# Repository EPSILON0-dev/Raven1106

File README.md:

# Raven1106

Raspberry Pi-like single board computer based on the Rockchip RV1106G3.

|  |  |
| - | - |
| | |

## Overview

Raven1106 is a custom open-hardware SBC. This repository contains everything
related to the project including: the board schematics and the PCB design, build
scripts, configurations, device trees and file system overlays for the
operating system images and all the patches needed to get everything working.

- CPU: Single-core Cortex-A7 @ 1.6 GHz
- RAM: 256MB DDR3L @ 924MHz
- Storage: SD card
- Ethernet: Full-size 100 MBit/s Ethernet port
- USB: Four USB-A ports routed through CH334F or one OTG USB-C port
- WiFi: ESP32C6 with ESP-Hosted firmware (_currently not functional_)
- Kernel: Linux 5.10 (Rockchip BSP)
- U-Boot: 2017.09 (Rockchip BSP)
- OS images: Debian 12 (bookworm, armhf)

## Why does it exist?

TLDR: It's a learning project

> The main goal of this project was to be a learning experience for designing complex high-speed digital PCBs. Creating an SBC that is almost capable enough to do basic tasks like hosting simple servers or running AI harnesses is a nice bonus. RV1106 was chosen specifically for its simplicity, integrated RAM meant no DDR routing and QFN package meant I could solder the board manually relatively easily.

> What this chip lacked in the hardware it made up for in the software side of things -- BSP is absolutely terrible, outdated, barely documented (_though with a lot of spelling mistakes_). Programming it wasn't much better either with only a few barely working flashing tools and a USB controller that might not actually be compliant with the USB spec, as most machines can't even enumerate it. It might have been genuinely easier to make this project around a more complex BGA part than this SoC.

## PCB

The board is designed in KiCad (4-layer). `pcb/` contains two revisions:

- `pcb/v1.0` — first revision
- `pcb/v1.1` — revision with component value fixes (no PCB layout changes)

| Layer 1 - Signal | Layer 2 - Ground Plane | Layer 3 - Power Planes | Layer 4 - Signal |
| :-: | :-: | :-: | :-: |
|  |  |  |  |

### Known v1.0 hardware issues and their fixes

**USB Impedance Miscalculation** - Turns out that FSUSB42MUX doesn't act as a retransmitter but like a normal switch which adds ~10 ohm impedance to the line. **Fix:** Swap `RN301` with 0-ohm and change `R301` and `R302` from 22 ohm to 10 ohm. This results the line impedance that is well in spec.

**No pullups on FSPI Flash** - Speaks for itself, thankfully the RV1106 has internal pull-ups that enable the chip and disable the write protection. And we don't even use it so it's a non-issue. _Cannot fix this without board changes._

**LED resistors too small** - The LEDs shine too brightly with 1k resistors. **Fix:** Change `R3`, `R4` and `R5` from 1k to 10k resistors.

**USB Hub crystal load too large** - The CH334F is designed to work with a crystal with no load caps, adding them causes the oscillation to die down. **Fix:** Change `R309` from 1k to 10 ohm, remove `C302` and `C303`.

**Boot button pull-up too strong** - With 1k the button does not affect the chip's boot at all. **Fix:** Change `R6` from 1k to 10k.

**Wrong ESP_BOOT pin exposed** - It should be pin 9, not pin 8. **Fix:** No way to fix it without modifying the board unfortunately, just flash the bootloader before soldering the ESP.

**Reference clock not connected to the camera** - Turns out not all camera modules have their own crystal oscillators. SC3336 requires a reference clock; RV1106 has two reference clock outputs, one of them is connected to the camera's reset and the other one to the IMU interrupt pin. **Fix:** Add a jumper from `R508` to `R515`.

> Most of these problems could have been prevented with "RTFM" (Reading The F***ing Manual).

## Repository layout

| Path | Contents |
|---|---|
| `configs/` | Defconfigs (kernel, U-Boot, crosstool-ng), device tree source, SD image layout, U-Boot env, user table |
| `kernel/` | Linux 5.10 Rockchip BSP kernel |
| `uboot/` | U-Boot 2017.09 Rockchip BSP |
| `debian/`, `overlayfs/` | Debian rootfs staging area and overlay |
| `crosstool-ng/`, `legacy-toolchain/` | Legacy uClibc toolchain (kernel/U-Boot builds) |
| `esp-hosted/` | ESP32-C6 host driver source (esp_hosted_ng) |
| `rkbin/` | Rockchip binary blobs (DDR init, trust) |
| `scripts/build.sh` | Image assembly, Debian rootfs, Docker environment |
| `images/` | Build artifacts and final `sdcard.img` |
| `pcb/` | KiCad hardware design |
| `docs/` | RV1106 datasheet / reference manuals |

## Building

### Build environment

All builds run inside a Docker container. The first invocation builds the
`rv1106-build` image, then drops you into a shell with the repository
mounted at `/work`:

```sh
make docker
```

### Toolchain

Before building any image build the legacy toolchain for the Kernel and U-Boot.
```sh
make toolchain
```

### Debian image

```sh
make            # default target: debian-image
# or explicitly:
make debian-image
```

> Known issue: If build fails on stage 2 debootstrap because of "Invalid format", just delete the `debian/` directory, restart the container and try to build again. _It does that sometimes..._

This builds the kernel, device tree, and U-Boot, then creates a Debian 12
(bookworm, armhf) rootfs with debootstrap (using qemu-user-static/binfmt for
the second stage) and assembles `images/sdcard.img`.

Notes:

- Default login: user `debian`, password `raven` (sudo user, SSH enabled).
  Override with the `BOARD_USER` and `DEBIAN_PASSWORD` environment variables.
- Included packages: systemd, ifupdown, openssh-server, sudo, dhcp client,
  busybox, vim-tiny, ca-certificates (see `DEBIAN_PACKAGES` in
  `scripts/build.sh`).
- Rootfs image size: 1 GB (`DEBIAN_ROOTFS_SIZE`).
- For now there's no autoresize, run `sudo resize2fs /dev/mmcblk1p5` after
  the first boot.

### Component targets

| Target | Description |
|---|---|
| `make kernel` | Build the kernel using the legacy toolchain |
| `make dtb` | Preprocess and compile `configs/device-tree.dts` into `images/` |
| `make uboot` | Build U-Boot (SPL + idblock + uboot.img) |
| `make espdriver` | Build the ESP32-C6 host driver against the kernel |
| `make toolchain` | Build the crosstool-ng uClibc toolchain |
| `make docker` | Build/enter the Docker build environment |
| `make *-clean` | Clean kernel / U-Boot build trees |

### Configuration targets

Each of these copies the stored defconfig from `configs/`, opens
`menuconfig`, and saves the result back to `configs/`:

```sh
make kernel-config
make uboot-config
make toolchain-config
```

## Output artifacts

All artifacts land in `images/`:

| File | Description |
|---|---|
| `sdcard.img` | Final flashable SD card image |
| `download.bin`, `idblock.img`, `uboot.img` | Bootloader stages |
| `Image`, `zImage`, `device-tree.dtb` | Kernel and device tree |
| `env.img` | U-Boot environment (from `configs/image-env.txt`) |
| `boot.vfat` | FAT32 boot partition (kernel + dtb) |
| `rootfs.ext4`, `rootfs.tar` | Root filesystem |

### SD card layout

The image has no MBR/GPT; partitions are defined by the kernel command line
(`blkdevparts`, see `configs/sdcard-image.cfg` and `configs/image-env.txt`):

| Partition | Offset | Size | Contents |
|---|---|---|---|
| env | 0x0 | 32 KiB | U-Boot environment |
| idblock | 0x8000 | 512 KiB | Rockchip ID block (SPL) |
| uboot | 0x88000 | 256 KiB | U-Boot |
| boot | 4 MiB | 64 MiB | FAT32: kernel image + device tree |
| rootfs | 68 MiB | remainder | ext4 root filesystem |

## Flashing and first boot

```sh
sudo dd if=images/sdcard.img of=/dev/sdX bs=4M status=progress conv=fsync
```

Serial console: `ttyFIQ0` at 115200 baud.

## WiFi setup

The WiFi interface (ESP32-C6 running ESP-Hosted firmware over SDIO) is set up
at boot on a running system, it is not configured during the image build. The
helper script `overlayfs/usr/local/bin/start-network` (installed on the image
at `/usr/local/bin/start-network`) performs the entire sequence:

1. **Module reset** - GPIO 2 is exported, pulsed low and released, which
   resets the ESP32. The pin is then unexported and the script waits 2 s.
2. **Driver loading** - the required modules are inserted from
   `/lib/modules/5.10.252/`: the crypto primitives (`libaes`, `libarc4`,
   `ecc`, `ecdh_generic`), `bluetooth`, the wireless stack (`cfg80211`) and
   finally the ESP-Hosted SDIO host driver (`esp32_sdio.ko`). The script then
   waits 5 s for the module to appear as `wlan0`.
   (The host driver is built separately with `make espdriver`.)
3. **Association** - `wpa_passphrase <ssid> <password>` generates a config
   into `/tmp/wpa.conf` and `wpa_supplicant -iwlan0` is started in the
   background, followed by a 15 s wait for the connection to come up.
4. **Addressing** - static IP configuration:
   `192.168.0.100/24` on `wlan0` with the default route via `192.168.0.1`.

### Configuring the network

The SSID, passphrase and addresses are hardcoded in
`/usr/local/bin/start-network`, so edit them on the board (or in
`overlayfs/usr/local/bin/start-network` and rebuild/flash the image):

```sh
sudo vi /usr/local/bin/start-network
```

Replace `ssid` and `password` in the `wpa_passphrase` call with your network
name and passphrase, and adjust the `ip addr add` and `ip route replace
default via` lines for your address and gateway. There is no DHCP client call
for `wlan0`.

### systemd service

The script runs automatically at boot via the systemd unit
`overlayfs/etc/systemd/system/start-network.service`
(`/etc/systemd/system/start-network.service` on the image) - a `oneshot`
service started after `network.target`, running as root with
`RemainAfterExit=yes`, and logging all output to `/tmp/wifi.log`. Use it to
start/stop the WiFi bring-up manually or to check the log:

```sh
sudo systemctl start start-network
sudo systemctl status start-network
less /tmp/wifi.log
```

> Note: the ESP32 must already carry the ESP-Hosted firmware (flash the
> bootloader/ESP before soldering it, see the PCB section above).

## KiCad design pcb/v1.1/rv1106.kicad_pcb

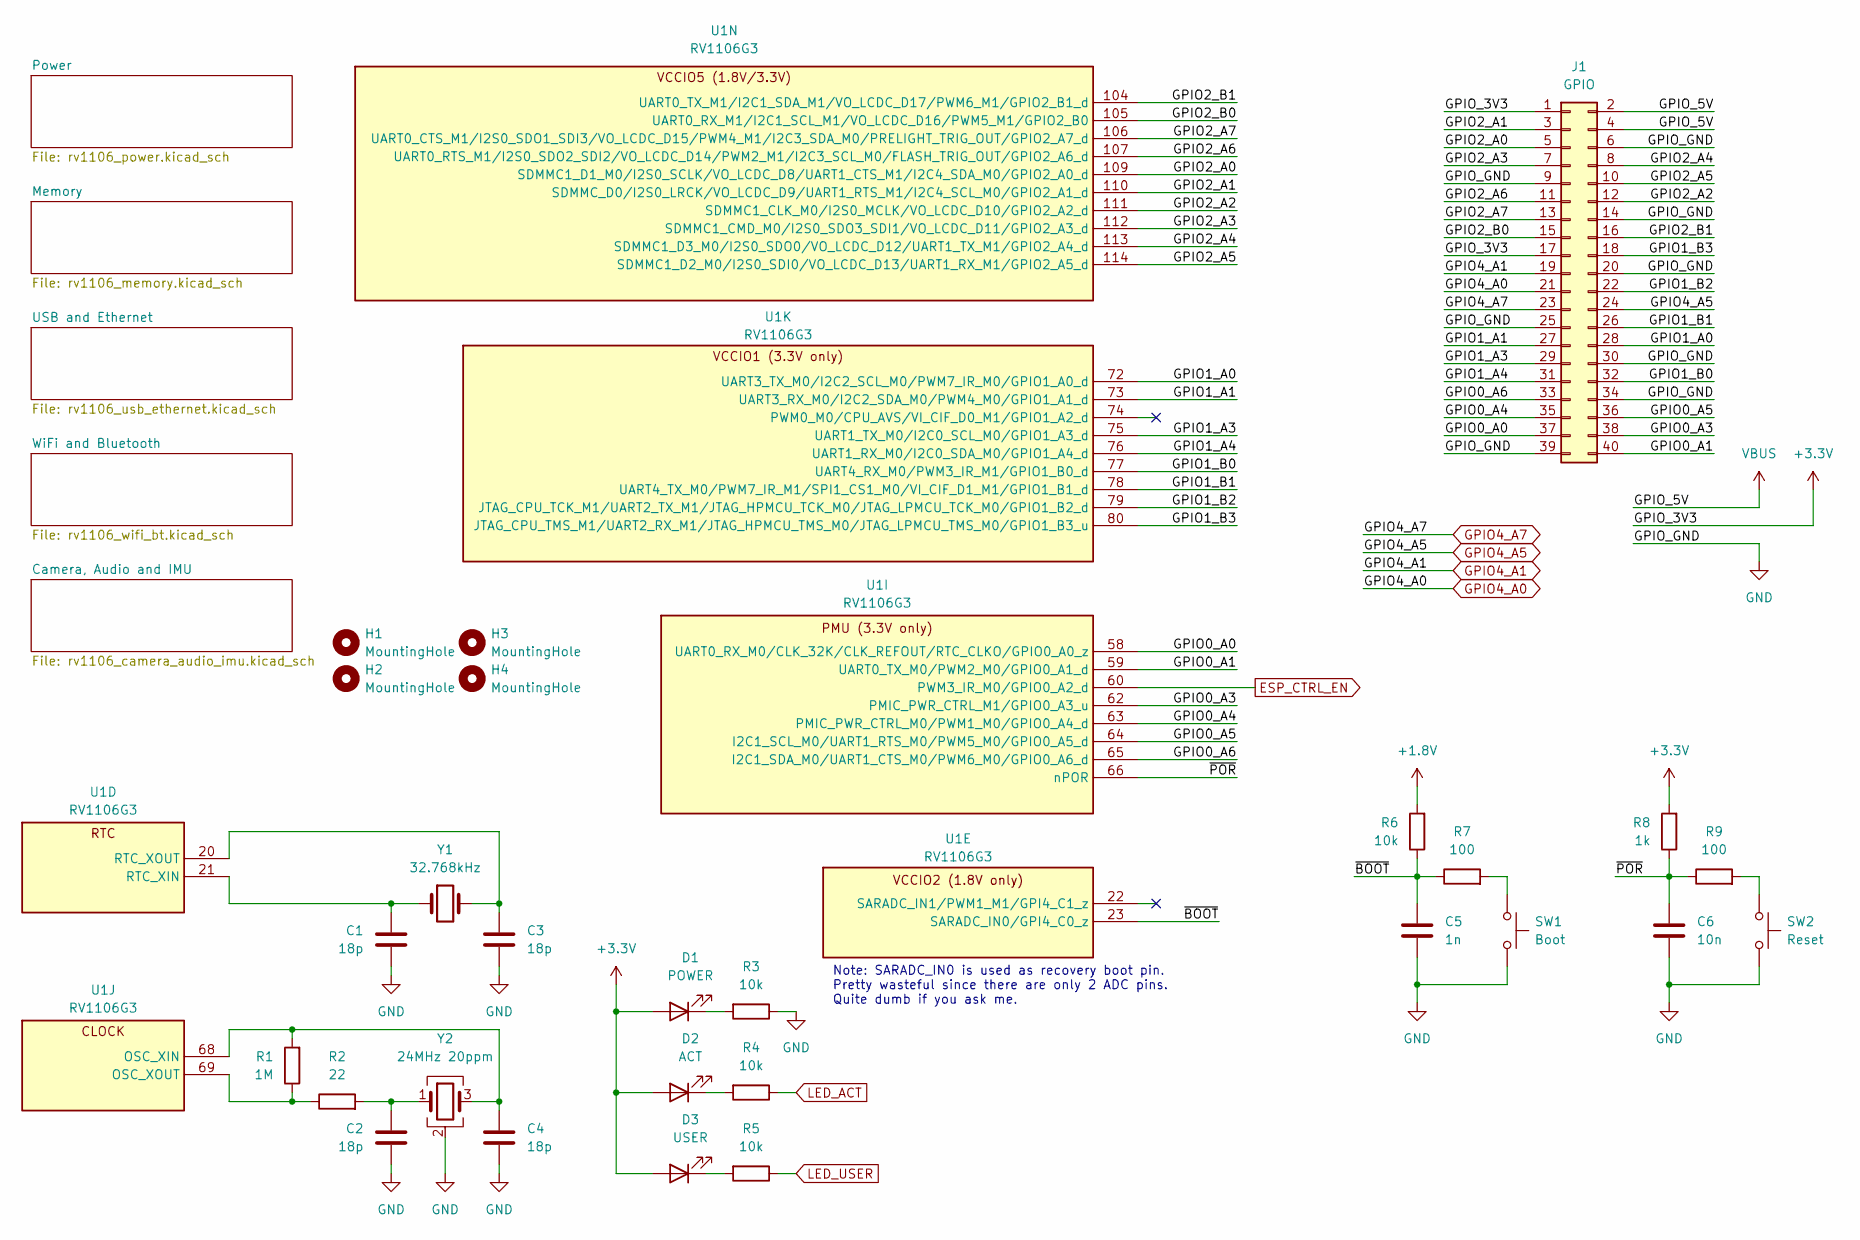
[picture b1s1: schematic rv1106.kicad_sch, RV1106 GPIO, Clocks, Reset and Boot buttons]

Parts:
C1, C2, C3, C4: 18p; C_0402_1005Metric; LCSC C7393840
C5: 1n; C_0402_1005Metric; LCSC C6119789
C6: 10n; C_0402_1005Metric; LCSC C696856
D1: POWER; LED_0603_1608Metric
D2: ACT; LED_0603_1608Metric
D3: USER; LED_0603_1608Metric
H1, H2, H3, H4: MountingHole; MountingHole_2.7mm_M2.5
J1: GPIO; PinHeader_2x20_P2.54mm_Vertical
R1: 1M; R_0402_1005Metric; LCSC C3017524
R2: 22; R_0402_1005Metric; LCSC C2929994
R3, R4, R5, R6: 10k; R_0402_1005Metric; LCSC C54531013
R7, R9: 100; R_0402_1005Metric; LCSC C54920716
R8: 1k; R_0402_1005Metric; LCSC C54531013
SW1: Boot; SW_Push_SPST_NO_Alps_SKRK
SW2: Reset; SW_Push_SPST_NO_Alps_SKRK
U1: RV1106G3; Rockchip_QFN-128-1EP_12.3x12.3mm_P0.35mm_EP7x7mm
Y1: 32.768kHz; Crystal_SMD_2012-2Pin_2.0x1.2mm; LCSC C2961989
Y2: 24MHz 20ppm; Crystal_SMD_2520-4Pin_2.5x2.0mm; LCSC C5261113

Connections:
+1.8V: R6.2; also elsewhere on the board
+3.3V: D1.2 (A), D2.2 (A), D3.2 (A), J1.1, J1.17, R8.2; also elsewhere on the board
/GPIO0_A0: J1.37, U1.58 (UART0_RX_M0/CLK_32K/CLK_REFOUT/RTC_CLKO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)
/GPIO0_A1: J1.40, U1.59 (UART0_TX_M0/PWM2_M0/GPIO0_A1_d)
/GPIO0_A3: J1.38, U1.62 (PMIC_PWR_CTRL_M1/GPIO0_A3_u)
/GPIO0_A4: J1.35, U1.63 (PMIC_PWR_CTRL_M0/PWM1_M0/GPIO0_A4_d)
/GPIO0_A5: J1.36, U1.64 (I2C1_SCL_M0/UART1_RTS_M0/PWM5_M0/GPIO0_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)
/GPIO0_A6: J1.33, U1.65 (I2C1_SDA_M0/UART1_CTS_M0/PWM6_M0/GPIO0_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)
/GPIO1_A0: J1.28, U1.72 (UART3_TX_M0/I2C2_SCL_M0/PWM7_IR_M0/GPIO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)
/GPIO1_A1: J1.27, U1.73 (UART3_RX_M0/I2C2_SDA_M0/PWM4_M0/GPIO1_A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)
/GPIO1_A3: J1.29, U1.75 (UART1_TX_M0/I2C0_SCL_M0/GPIO1_A3_d)
/GPIO1_A4: J1.31, U1.76 (UART1_RX_M0/I2C0_SDA_M0/GPIO1_A4_d)
/GPIO1_B0: J1.32, U1.77 (UART4_RX_M0/PWM3_IR_M1/GPIO1_B0_d)
/GPIO1_B1: J1.26, U1.78 (UART4_TX_M0/PWM7_IR_M1/SPI1_CS1_M0/VI_C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)
/GPIO1_B2: J1.22, U1.79 (JTAG_CPU_TCK_M1/UART2_TX_M1/JTAG_HPMCU_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)
/GPIO1_B3: J1.18, U1.80 (JTAG_CPU_TMS_M1/UART2_RX_M1/JTAG_HPMCU_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)
/GPIO2_A0: J1.5, U1.109 (SDMMC1_D1_M0/I2S0_SCLK/VO_LCDC_D8/UART1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)
/GPIO2_A1: J1.3, U1.110 (SDMMC_D0/I2S0_LRCK/VO_LCDC_D9/UART1_RTS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)
/GPIO2_A2: J1.12, U1.111 (SDMMC1_CLK_M0/I2S0_MCLK/VO_LCDC_D10/GPI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)
/GPIO2_A3: J1.7, U1.112 (SDMMC1_CMD_M0/I2S0_SDO3_SDI1/VO_LCDC_D1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)
/GPIO2_A4: J1.8, U1.113 (SDMMC1_D3_M0/I2S0_SDO0/VO_LCDC_D12/UART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)
/GPIO2_A5: J1.10, U1.114 (SDMMC1_D2_M0/I2S0_SDI0/VO_LCDC_D13/UART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)
/GPIO2_A6: J1.11, U1.107 (UART0_RTS_M1/I2S0_SDO2_SDI2/VO_LCDC_D14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)
/GPIO2_A7: J1.13, U1.106 (UART0_CTS_M1/I2S0_SDO1_SDI3/VO_LCDC_D15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)
/GPIO2_B0: J1.15, U1.105 (UART0_RX_M1/I2C1_SCL_M1/VO_LCDC_D16/PWM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)
/GPIO2_B1: J1.16, U1.104 (UART0_TX_M1/I2C1_SDA_M1/VO_LCDC_D17/PWM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)
/~BOOT: C5.1, R6.1, R7.1, U1.23 (SARADC_IN0/GPI4_C0_z)
/~POR: C6.1, R8.1, R9.1, U1.66 (nPOR)
ESP_CTRL_EN: U1.60 (PWM3_IR_M0/GPIO0_A2_d); also elsewhere on the board
GND: C1.2, C2.2, C3.2, C4.2, C5.2, C6.2, J1.6, J1.9, J1.14, J1.20, J1.25, J1.30, J1.34, J1.39, R3.1, SW1.2, SW2.2, Y2.2 (G), Y2.4 (G); also elsewhere on the board
GPIO4_A0: J1.21; also elsewhere on the board
GPIO4_A1: J1.19; also elsewhere on the board
GPIO4_A5: J1.24; also elsewhere on the board
GPIO4_A7: J1.23; also elsewhere on the board
LED_ACT: R4.1; also elsewhere on the board
LED_USER: R5.1; also elsewhere on the board
unnamed: C2.1, R2.2, Y2.1
unnamed: D1.1 (K), R3.2
unnamed: D2.1 (K), R4.2
unnamed: D3.1 (K), R5.2
unnamed: R7.2, SW1.1
unnamed: R9.2, SW2.1
unnamed: C4.1, R1.2, U1.68 (OSC_XIN), Y2.3
unnamed: R1.1, R2.1, U1.69 (OSC_XOUT)
unnamed: C1.1, U1.21 (RTC_XIN), Y1.1
unnamed: C3.1, U1.20 (RTC_XOUT), Y1.2
VBUS: J1.2, J1.4; also elsewhere on the board

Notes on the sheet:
Note: SARADC_IN0 is used as recovery boot pin. Pretty wasteful since there are only 2 ADC pins. Quite dumb if you ask me.

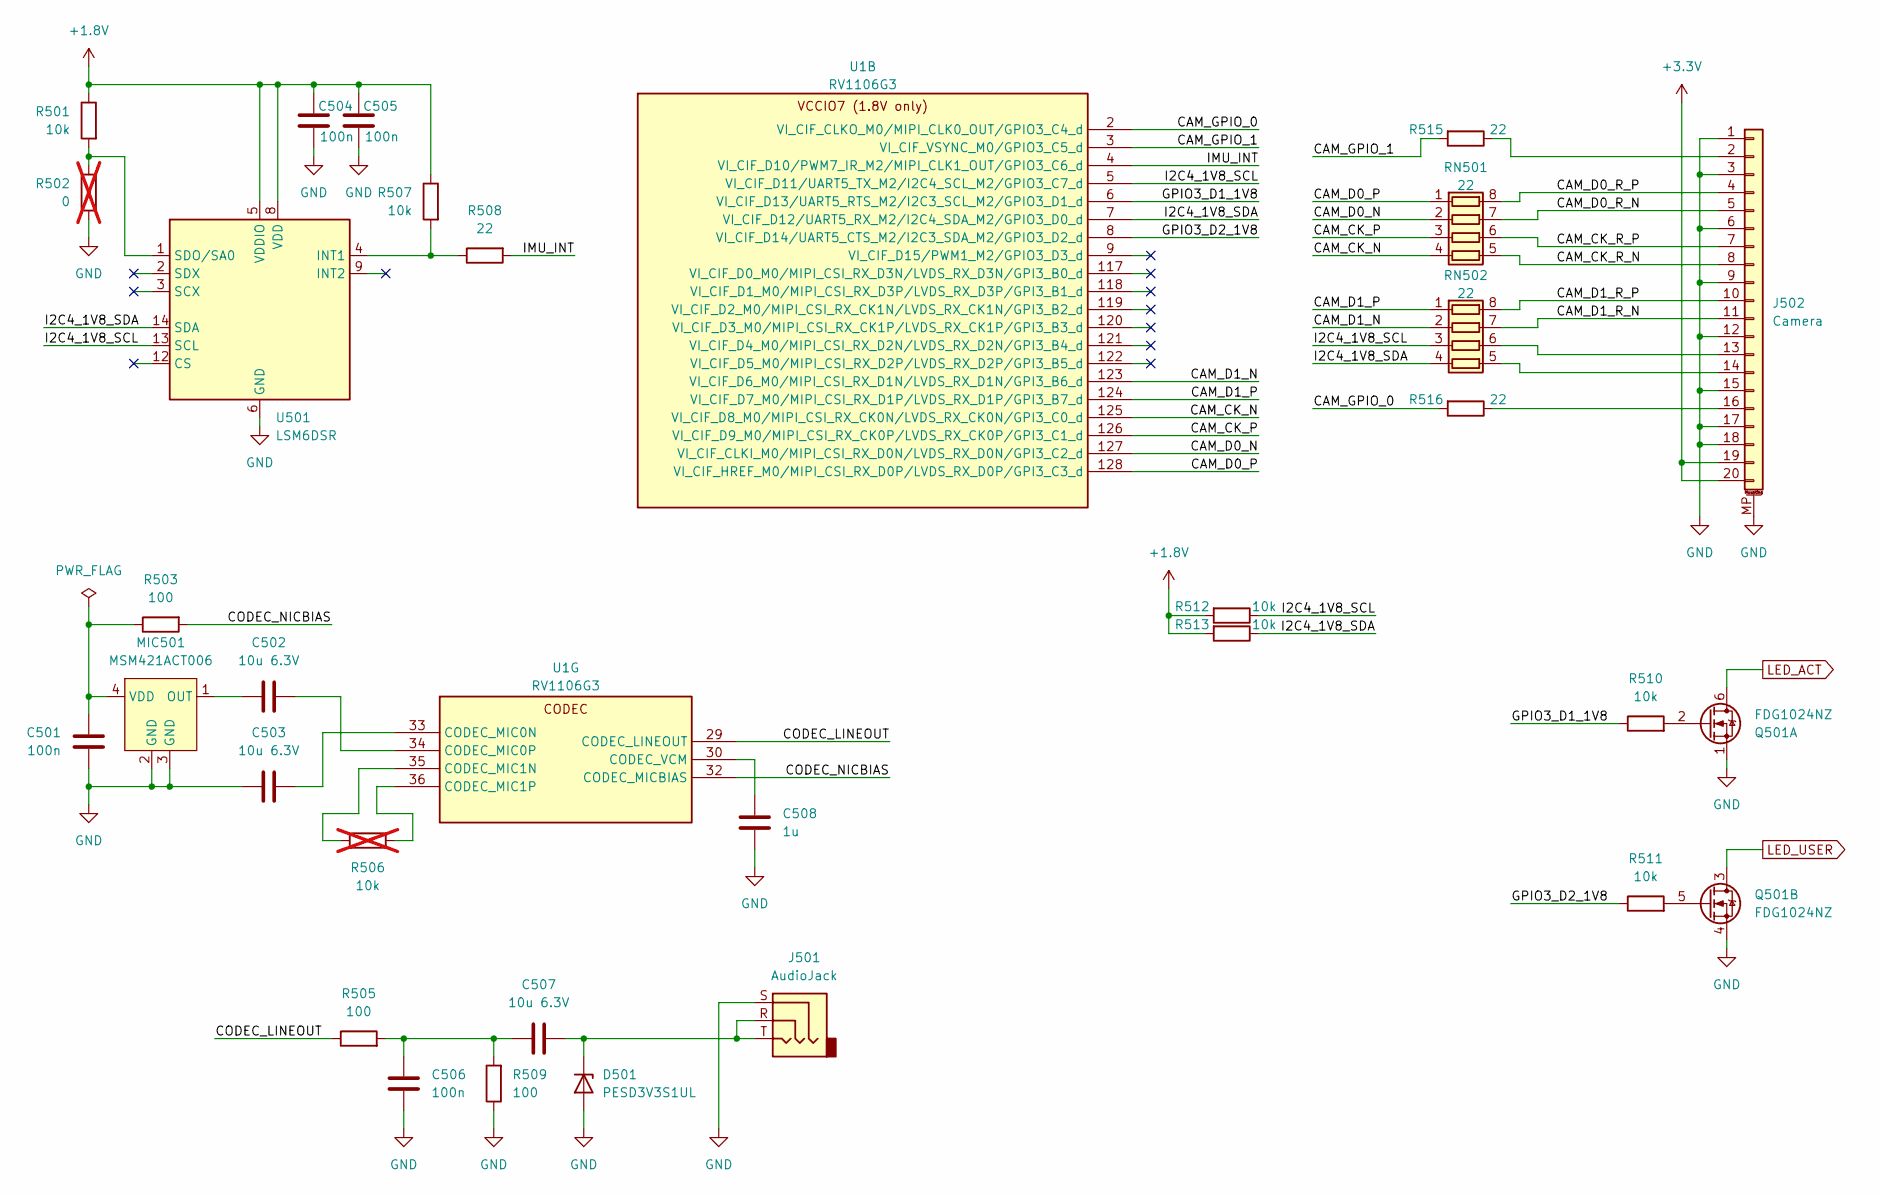
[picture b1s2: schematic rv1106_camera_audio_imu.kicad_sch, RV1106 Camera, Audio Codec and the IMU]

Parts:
C501, C504, C505, C506: 100n; C_0402_1005Metric; LCSC C3839219
C502, C503, C507: 10u 6.3V; C_0603_1608Metric; LCSC C1691
C508: 1u; C_0402_1005Metric; LCSC C380293
D501: PESD3V3S1UL; D_SOD-882; LCSC C70371
J501: AudioJack; Jack_3.5mm_CUI_SJ-3523-SMT_Horizontal; LCSC C4991872
J502: Camera; FPC_20_0.5mm_MP_BottomSide; LCSC C51364851
MIC501: MSM421ACT006; LGA4-1.9x2.8; LCSC C51928207
Q501: FDG1024NZ; SOT-363_SC-70-6; LCSC C51886163
R501, R507, R510, R511, R512, R513: 10k; R_0402_1005Metric; LCSC C54531014
R502: 0; R_0402_1005Metric; not fitted
R503, R505, R509: 100; R_0402_1005Metric; LCSC C54920716
R506: 10k; R_0402_1005Metric; not fitted
R508, R515, R516: 22; R_0402_1005Metric; LCSC C2929994
RN501, RN502: 22; R_Array_Convex_4x0402; LCSC C168184
U1: RV1106G3; Rockchip_QFN-128-1EP_12.3x12.3mm_P0.35mm_EP7x7mm
U501: LSM6DSR; LGA-14_3x2.5mm_P0.5mm_LayoutBorder3x4y

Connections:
+1.8V: C504.1, C505.1, R501.1, R507.1, R512.2, R513.2, U501.5 (VDDIO), U501.8 (VDD); also elsewhere on the board
+3.3V: J502.19, J502.20; also elsewhere on the board
/Camera, Audio and IMU/CAM_CK_N: RN501.4 (R4.1), U1.125 (VI_CIF_D8_M0/MIPI_CSI_RX_CK0N/LVDS_RX_C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)
/Camera, Audio and IMU/CAM_CK_P: RN501.3 (R3.1), U1.126 (VI_CIF_D9_M0/MIPI_CSI_RX_CK0P/LVDS_RX_C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)
/Camera, Audio and IMU/CAM_CK_R_N: J502.8, RN501.5 (R4.2)
/Camera, Audio and IMU/CAM_CK_R_P: J502.7, RN501.6 (R3.2)
/Camera, Audio and IMU/CAM_D0_N: RN501.2 (R2.1), U1.127 (VI_CIF_CLKI_M0/MIPI_CSI_RX_D0N/LVDS_RX_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)
/Camera, Audio and IMU/CAM_D0_P: RN501.1 (R1.1), U1.128 (VI_CIF_HREF_M0/MIPI_CSI_RX_D0P/LVDS_RX_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)
/Camera, Audio and IMU/CAM_D0_R_N: J502.5, RN501.7 (R2.2)
/Camera, Audio and IMU/CAM_D0_R_P: J502.4, RN501.8 (R1.2)
/Camera, Audio and IMU/CAM_D1_N: RN502.2 (R2.1), U1.123 (VI_CIF_D6_M0/MIPI_CSI_RX_D1N/LVDS_RX_D1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)
/Camera, Audio and IMU/CAM_D1_P: RN502.1 (R1.1), U1.124 (VI_CIF_D7_M0/MIPI_CSI_RX_D1P/LVDS_RX_D1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)
/Camera, Audio and IMU/CAM_D1_R_N: J502.11, RN502.7 (R2.2)
/Camera, Audio and IMU/CAM_D1_R_P: J502.10, RN502.8 (R1.2)
/Camera, Audio and IMU/CAM_GPIO_0: R516.2, U1.2 (VI_CIF_CLKO_M0/MIPI_CLK0_OUT/GPIO3_C4_d)
/Camera, Audio and IMU/CAM_GPIO_1: R515.2, U1.3 (VI_CIF_VSYNC_M0/GPIO3_C5_d)
/Camera, Audio and IMU/CODEC_LINEOUT: R505.1, U1.29 (CODEC_LINEOUT)
/Camera, Audio and IMU/CODEC_NICBIAS: R503.2, U1.32 (CODEC_MICBIAS)
/Camera, Audio and IMU/GPIO3_D1_1V8: R510.1, U1.6 (VI_CIF_D13/UART5_RTS_M2/I2C3_SCL_M2/GPI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)
/Camera, Audio and IMU/GPIO3_D2_1V8: R511.1, U1.8 (VI_CIF_D14/UART5_CTS_M2/I2C3_SDA_M2/GPI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)
/Camera, Audio and IMU/I2C4_1V8_SCL: R512.1, RN502.3 (R3.1), U1.5 (VI_CIF_D11/UART5_TX_M2/I2C4_SCL_M2/GPIO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), U501.13 (SCL)
/Camera, Audio and IMU/I2C4_1V8_SDA: R513.1, RN502.4 (R4.1), U1.7 (VI_CIF_D12/UART5_RX_M2/I2C4_SDA_M2/GPIO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), U501.14 (SDA)
/Camera, Audio and IMU/IMU_INT: R508.2, U1.4 (VI_CIF_D10/PWM7_IR_M2/MIPI_CLK1_OUT/GPI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)
GND: C501.2, C503.1, C504.2, C505.2, C506.2, C508.1, D501.2 (A), J501.S, J502.1, J502.3, J502.6, J502.9, J502.12, J502.15, J502.17, J502.18, J502.MP (MountPin), MIC501.2 (GND), MIC501.3 (GND), Q501.1 (S), Q501.4 (S), R502.2, R509.1, U501.6 (GND), U501.7 (GND); also elsewhere on the board
LED_ACT: Q501.6 (D); also elsewhere on the board
LED_USER: Q501.3 (D); also elsewhere on the board
unnamed: C506.1, C507.1, R505.2, R509.2
unnamed: C507.2, D501.1 (K), J501.R, J501.T
unnamed: J502.2, R515.1
unnamed: J502.13, RN502.6 (R3.2)
unnamed: J502.14, RN502.5 (R4.2)
unnamed: J502.16, R516.1
unnamed: C502.1, MIC501.1 (OUT)
unnamed: C501.1, MIC501.4 (VDD), R503.1
unnamed: Q501.2 (G), R510.2
unnamed: Q501.5 (G), R511.2
unnamed: C503.2, U1.33 (CODEC_MIC0N)
unnamed: C502.2, U1.34 (CODEC_MIC0P)
unnamed: R506.1, U1.35 (CODEC_MIC1N)
unnamed: R506.2, U1.36 (CODEC_MIC1P)
unnamed: C508.2, U1.30 (CODEC_VCM)
unnamed: R507.2, R508.1, U501.4 (INT1)
unnamed: R501.2, R502.1, U501.1 (SDO/SA0)

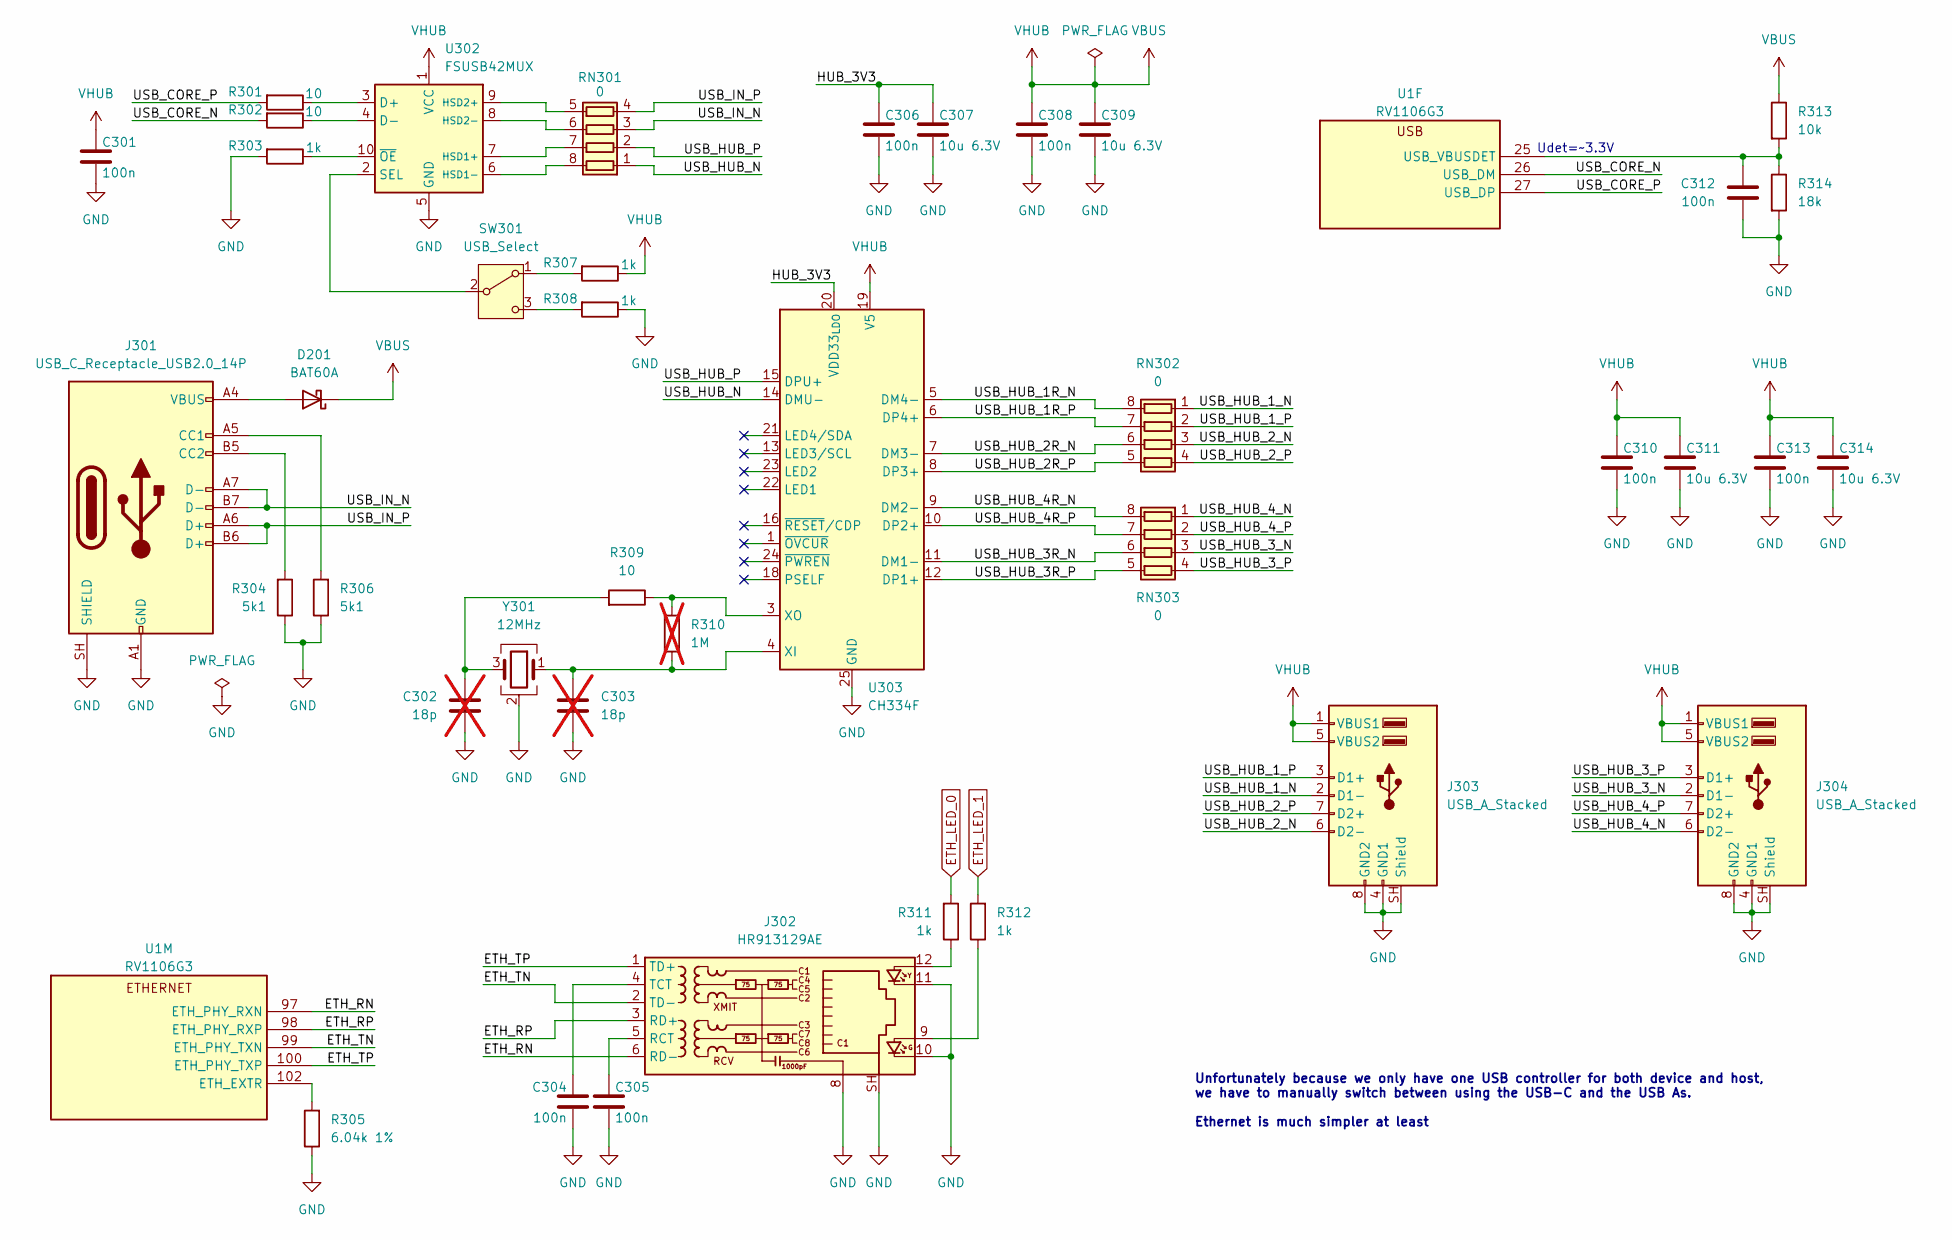
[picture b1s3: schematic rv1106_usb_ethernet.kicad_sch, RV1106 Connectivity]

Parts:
C301, C304, C305, C306, C308, C310, C312, C313: 100n; C_0402_1005Metric; LCSC C3839219
C302, C303: 18p; C_0402_1005Metric; LCSC C7393840; not fitted
C307, C309, C311, C314: 10u 6.3V; C_0603_1608Metric; LCSC C1691
D201: BAT60A; D_SOD-323; LCSC C5355496
J301: USB_C_Receptacle_USB2.0_14P; USB_C_Receptacle_G-Switch_GT-USB-7010ASV
J302: HR913129AE; RJ45_Hanrun_HR911105A_Horizontal; LCSC C95663
J303, J304: USB_A_Stacked; USB_A_Wuerth_61400826021_Horizontal_Stacked; LCSC C456021
R301, R302: 10; R_0402_1005Metric; LCSC C2929994
R303, R307, R308, R311, R312: 1k; R_0402_1005Metric; LCSC C54531013
R304, R306: 5k1; R_0402_1005Metric; LCSC C53224182
R305: 6.04k 1%; R_0402_1005Metric; LCSC C881060
R309: 10; R_0402_1005Metric; LCSC C54531013
R310: 1M; R_0402_1005Metric; not fitted
R313: 10k; R_0402_1005Metric; LCSC C54531014
R314: 18k; R_0402_1005Metric; LCSC C49653003
RN301, RN302, RN303: 0; R_Array_Convex_4x0402; LCSC C168184
SW301: USB_Select; SW_SPDT_PCM12
U1: RV1106G3; Rockchip_QFN-128-1EP_12.3x12.3mm_P0.35mm_EP7x7mm
U302: FSUSB42MUX; MSOP-10_3x3mm_P0.5mm; LCSC C11355
U303: CH334F; QFN-24-1EP_4x4mm_P0.5mm_EP2.7x2.7mm; LCSC C5187527
Y301: 12MHz; Crystal_SMD_2520-4Pin_2.5x2.0mm; LCSC C5261113

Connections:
/USB and Ethernet/ETH_RN: J302.6 (RD-), U1.97 (ETH_PHY_RXN)
/USB and Ethernet/ETH_RP: J302.3 (RD+), U1.98 (ETH_PHY_RXP)
/USB and Ethernet/ETH_TN: J302.2 (TD-), U1.99 (ETH_PHY_TXN)
/USB and Ethernet/ETH_TP: J302.1 (TD+), U1.100 (ETH_PHY_TXP)
/USB and Ethernet/HUB_3V3: C306.1, C307.1, U303.20 (VDD33_{LDO})
/USB and Ethernet/USB_CORE_N: R302.2, U1.26 (USB_DM)
/USB and Ethernet/USB_CORE_P: R301.2, U1.27 (USB_DP)
/USB and Ethernet/USB_HUB_1R_N: RN302.8 (R1.2), U303.5 (DM4-)
/USB and Ethernet/USB_HUB_1R_P: RN302.7 (R2.2), U303.6 (DP4+)
/USB and Ethernet/USB_HUB_1_N: J303.2 (D1-), RN302.1 (R1.1)
/USB and Ethernet/USB_HUB_1_P: J303.3 (D1+), RN302.2 (R2.1)
/USB and Ethernet/USB_HUB_2R_N: RN302.6 (R3.2), U303.7 (DM3-)
/USB and Ethernet/USB_HUB_2R_P: RN302.5 (R4.2), U303.8 (DP3+)
/USB and Ethernet/USB_HUB_2_N: J303.6 (D2-), RN302.3 (R3.1)
/USB and Ethernet/USB_HUB_2_P: J303.7 (D2+), RN302.4 (R4.1)
/USB and Ethernet/USB_HUB_3R_N: RN303.6 (R3.2), U303.11 (DM1-)
/USB and Ethernet/USB_HUB_3R_P: RN303.5 (R4.2), U303.12 (DP1+)
/USB and Ethernet/USB_HUB_3_N: J304.2 (D1-), RN303.3 (R3.1)
/USB and Ethernet/USB_HUB_3_P: J304.3 (D1+), RN303.4 (R4.1)
/USB and Ethernet/USB_HUB_4R_N: RN303.8 (R1.2), U303.9 (DM2-)
/USB and Ethernet/USB_HUB_4R_P: RN303.7 (R2.2), U303.10 (DP2+)
/USB and Ethernet/USB_HUB_4_N: J304.6 (D2-), RN303.1 (R1.1)
/USB and Ethernet/USB_HUB_4_P: J304.7 (D2+), RN303.2 (R2.1)
/USB and Ethernet/USB_HUB_N: RN301.1 (R1.1), U303.14 (DMU-)
/USB and Ethernet/USB_HUB_P: RN301.2 (R2.1), U303.15 (DPU+)
/USB and Ethernet/USB_IN_N: J301.A7 (D-), J301.B7 (D-), RN301.3 (R3.1)
/USB and Ethernet/USB_IN_P: J301.A6 (D+), J301.B6 (D+), RN301.4 (R4.1)
ETH_LED_0: R311.2; also elsewhere on the board
ETH_LED_1: R312.2; also elsewhere on the board
GND: C301.2, C302.2, C303.2, C304.2, C305.2, C306.2, C307.2, C308.2, C309.2, C310.2, C311.2, C312.2, C313.2, C314.2, J301.A1 (GND), J301.A12 (GND), J301.B1 (GND), J301.B12 (GND), J301.SH (SHIELD), J302.8, J302.10, J302.11, J302.SH, J303.4 (GND1), J303.8 (GND2), J303.SH (Shield), J304.4 (GND1), J304.8 (GND2), J304.SH (Shield), R303.2, R304.1, R305.1, R306.1, R308.1, R314.2, U302.5 (GND), U303.25 (GND), Y301.2 (G), Y301.4 (G); also elsewhere on the board
unnamed: C302.1, R309.2, Y301.3
unnamed: D201.2 (A), J301.A4 (VBUS), J301.A9 (VBUS), J301.B4 (VBUS), J301.B9 (VBUS)
unnamed: J301.A5 (CC1), R306.2
unnamed: J301.B5 (CC2), R304.2
unnamed: J302.9, R312.1
unnamed: J302.12, R311.1
unnamed: C305.1, J302.5 (RCT)
unnamed: C304.1, J302.4 (TCT)
unnamed: RN301.8 (R1.2), U302.6 (HSD1-)
unnamed: RN301.7 (R2.2), U302.7 (HSD1+)
unnamed: RN301.6 (R3.2), U302.8 (HSD2-)
unnamed: RN301.5 (R4.2), U302.9 (HSD2+)
unnamed: R307.2, SW301.1 (A)
unnamed: SW301.2 (B), U302.2 (SEL)
unnamed: R308.2, SW301.3 (C)
unnamed: R305.2, U1.102 (ETH_EXTR)
unnamed: C312.1, R313.2, R314.1, U1.25 (USB_VBUSDET)
unnamed: R301.1, U302.3 (D+)
unnamed: R302.1, U302.4 (D-)
unnamed: R303.1, U302.10 (~OE)
unnamed: C303.1, R310.1, U303.4 (XI), Y301.1
unnamed: R309.1, R310.2, U303.3 (XO)
VBUS: C301.1, C308.1, C309.1, C310.1, C311.1, C313.1, C314.1, D201.1 (K), J303.1 (VBUS1), J303.5 (VBUS2), J304.1 (VBUS1), J304.5 (VBUS2), R307.1, R313.1, U302.1 (VCC), U303.19 (V5); also elsewhere on the board

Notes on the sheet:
Udet=~3.3V
Unfortunately because we only have one USB controller for both device and host, we have to manually switch between using the USB-C and the USB As. Ethernet is much simpler at least

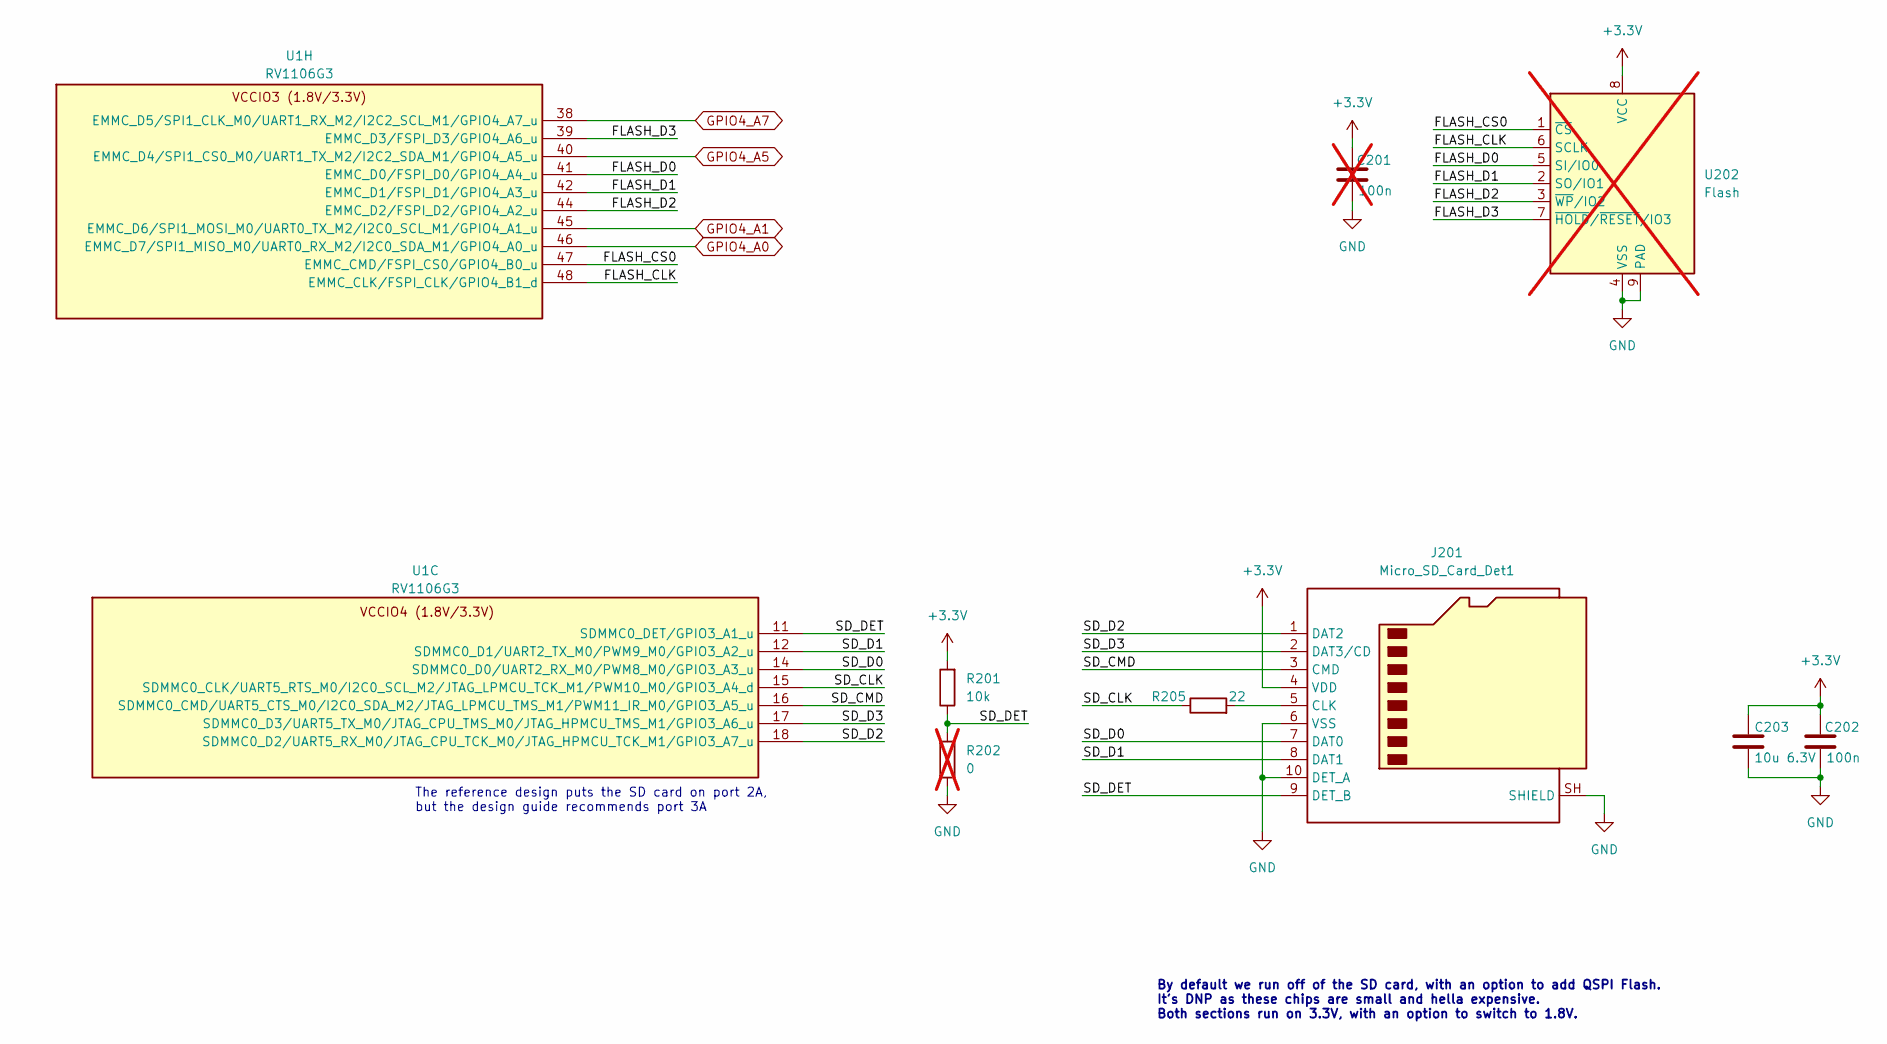
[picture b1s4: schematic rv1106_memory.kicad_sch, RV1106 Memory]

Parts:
C201: 100n; C_0402_1005Metric; LCSC C3839219; not fitted
C202: 100n; C_0402_1005Metric; LCSC C3839219
C203: 10u 6.3V; C_0603_1608Metric; LCSC C1691
J201: Micro_SD_Card_Det1; microSD_HC_Hirose_DM3D-SF; LCSC C719027
R201: 10k; R_0402_1005Metric; LCSC C54531014
R202: 0; R_0402_1005Metric; not fitted
R205: 22; R_0402_1005Metric; LCSC C2929994
U1: RV1106G3; Rockchip_QFN-128-1EP_12.3x12.3mm_P0.35mm_EP7x7mm
U202: Flash; WSON-8-1EP_8x6mm_P1.27mm_EP3.4x4.3mm; not fitted

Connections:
+3.3V: C201.1, C202.1, C203.1, J201.4 (VDD), R201.2, U202.8 (VCC); also elsewhere on the board
/Memory/FLASH_CLK: U1.48 (EMMC_CLK/FSPI_CLK/GPIO4_B1_d), U202.6 (SCLK)
/Memory/FLASH_CS0: U1.47 (EMMC_CMD/FSPI_CS0/GPIO4_B0_u), U202.1 (~CS)
/Memory/FLASH_D0: U1.41 (EMMC_D0/FSPI_D0/GPIO4_A4_u), U202.5 (SI/IO0)
/Memory/FLASH_D1: U1.42 (EMMC_D1/FSPI_D1/GPIO4_A3_u), U202.2 (SO/IO1)
/Memory/FLASH_D2: U1.44 (EMMC_D2/FSPI_D2/GPIO4_A2_u), U202.3 (~WP/IO2)
/Memory/FLASH_D3: U1.39 (EMMC_D3/FSPI_D3/GPIO4_A6_u), U202.7 (~HOLD/~RESET/IO3)
/Memory/SD_CLK: R205.1, U1.15 (SDMMC0_CLK/UART5_RTS_M0/I2C0_SCL_M2/JTA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)
/Memory/SD_CMD: J201.3 (CMD), U1.16 (SDMMC0_CMD/UART5_CTS_M0/I2C0_SDA_M2/JTA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)
/Memory/SD_D0: J201.7 (DAT0), U1.14 (SDMMC0_D0/UART2_RX_M0/PWM8_M0/GPIO3_A3_u)
/Memory/SD_D1: J201.8 (DAT1), U1.12 (SDMMC0_D1/UART2_TX_M0/PWM9_M0/GPIO3_A2_u)
/Memory/SD_D2: J201.1 (DAT2), U1.18 (SDMMC0_D2/UART5_RX_M0/JTAG_CPU_TCK_M0/J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)
/Memory/SD_D3: J201.2 (DAT3/CD), U1.17 (SDMMC0_D3/UART5_TX_M0/JTAG_CPU_TMS_M0/J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)
/Memory/SD_DET: J201.9 (DET_B), R201.1, R202.2, U1.11 (SDMMC0_DET/GPIO3_A1_u)
GND: C201.2, C202.2, C203.2, J201.6 (VSS), J201.10 (DET_A), J201.SH (SHIELD), R202.1, U202.4 (VSS), U202.9 (PAD); also elsewhere on the board
GPIO4_A0: U1.46 (EMMC_D7/SPI1_MISO_M0/UART0_RX_M2/I2C0_S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); also elsewhere on the board
GPIO4_A1: U1.45 (EMMC_D6/SPI1_MOSI_M0/UART0_TX_M2/I2C0_S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); also elsewhere on the board
GPIO4_A5: U1.40 (EMMC_D4/SPI1_CS0_M0/UART1_TX_M2/I2C2_SD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); also elsewhere on the board
GPIO4_A7: U1.38 (EMMC_D5/SPI1_CLK_M0/UART1_RX_M2/I2C2_SC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); also elsewhere on the board
unnamed: J201.5 (CLK), R205.2

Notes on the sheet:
By default we run off of the SD card, with an option to add QSPI Flash. It's DNP as these chips are small and hella expensive. Both sections run on 3.3V, with an option to switch to 1.8V.
The reference design puts the SD card on port 2A, but the design guide recommends port 3A
